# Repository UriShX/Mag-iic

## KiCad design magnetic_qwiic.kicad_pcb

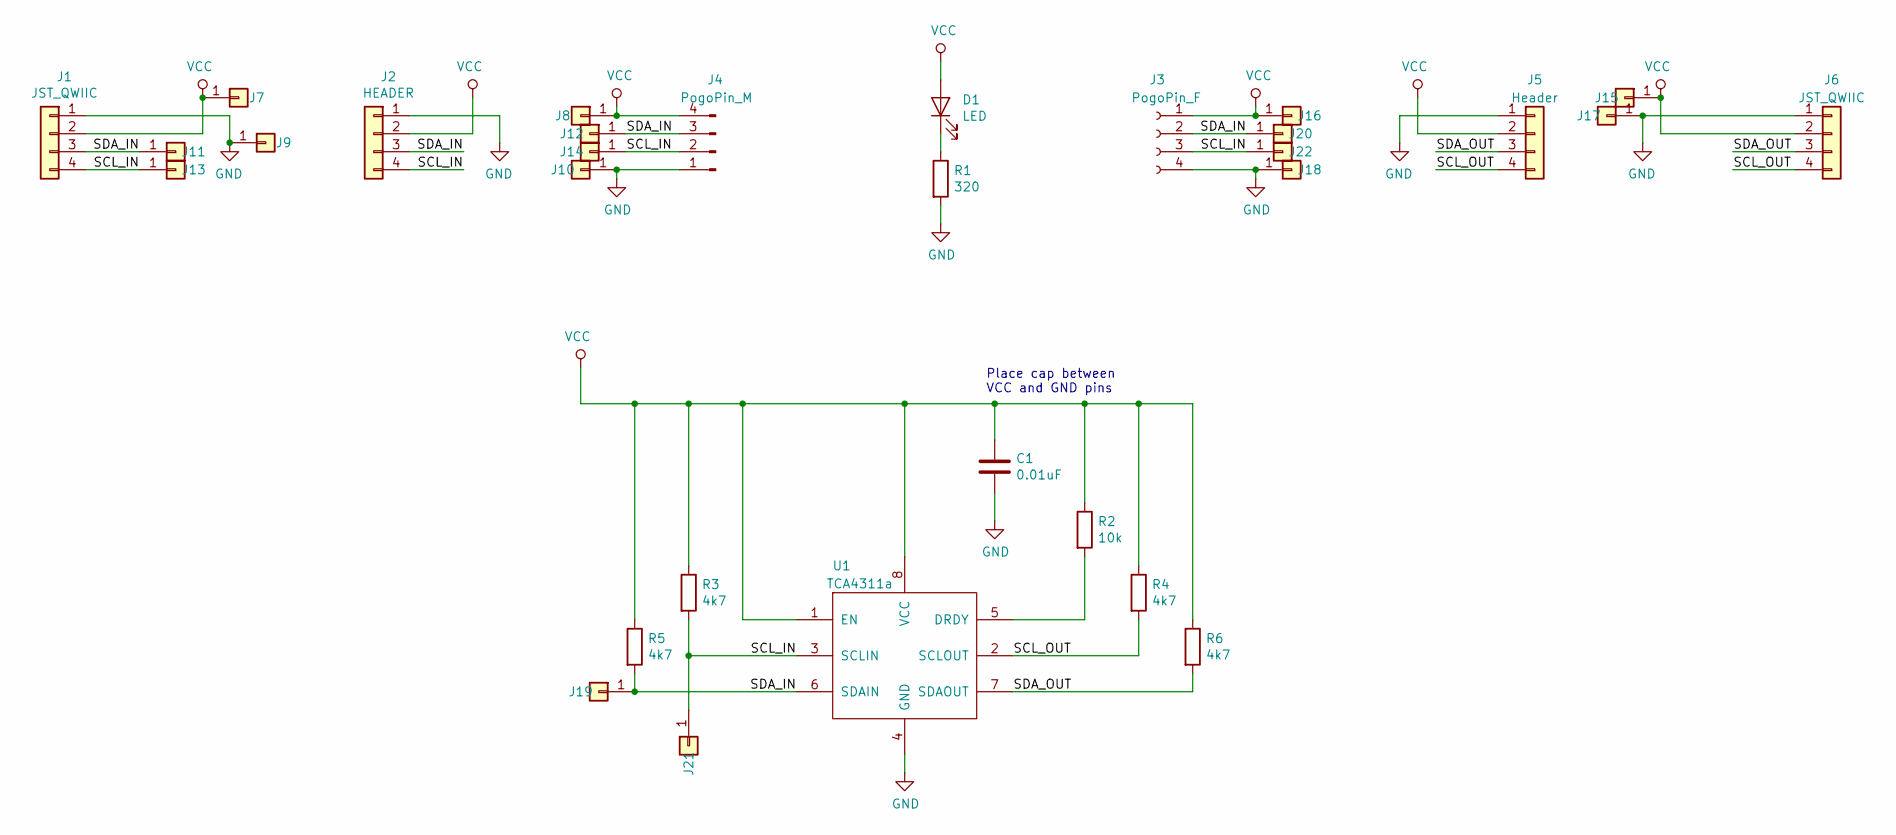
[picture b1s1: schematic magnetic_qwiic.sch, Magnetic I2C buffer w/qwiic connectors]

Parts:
C1: 0.01uF; C_0805_HandSoldering
D1: LED; LED_1206_HandSoldering
J1, J6: JST_QWIIC; JST_SH_SM04B-SRSS-TB_04x1.00mm_Angled
J2: HEADER; Pin_Header_Straight_1x04_Pitch2.54mm
J3: PogoPin_F; QWIIC_PP
J4: PogoPin_M; QWIIC_PP
J5: Header; Pin_Header_Straight_1x04_Pitch2.54mm
J7, J8, J9, J10, J11, J12, J13, J14, J15, J16, J17, J18, J19, J20, J21, J22: Conn_01x01; SMD_pad_for_fillet_solder
R1: 320; R_0805_HandSoldering
R2: 10k; R_0805_HandSoldering
R3, R4, R5, R6: 4k7; R_0805_HandSoldering
U1: TCA4311a; SOIC-8_3.9x4.9mm_Pitch1.27mm

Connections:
/SCL_IN: J1.4, J2.4, J3.3, J4.2, J13.1, J14.1, J21.1, J22.1, R3.2, U1.3 (SCLIN)
/SCL_OUT: J5.4, J6.4, R4.2, U1.2 (SCLOUT)
/SDA_IN: J1.3, J2.3, J3.2, J4.3, J11.1, J12.1, J19.1, J20.1, R5.2, U1.6 (SDAIN)
/SDA_OUT: J5.3, J6.3, R6.2, U1.7 (SDAOUT)
GND: C1.2, J1.1, J2.1, J3.4, J4.1, J5.1, J6.1, J9.1, J10.1, J17.1, J18.1, R1.2, U1.4 (GND)
unnamed: D1.1 (K), R1.1
unnamed: R2.2, U1.5 (DRDY)
VCC: C1.1, D1.2 (A), J1.2, J2.2, J3.1, J4.4, J5.2, J6.2, J7.1, J8.1, J15.1, J16.1, R2.1, R3.1, R4.1, R5.1, R6.1, U1.1 (EN), U1.8 (VCC)

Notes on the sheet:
Place cap between VCC and GND pins

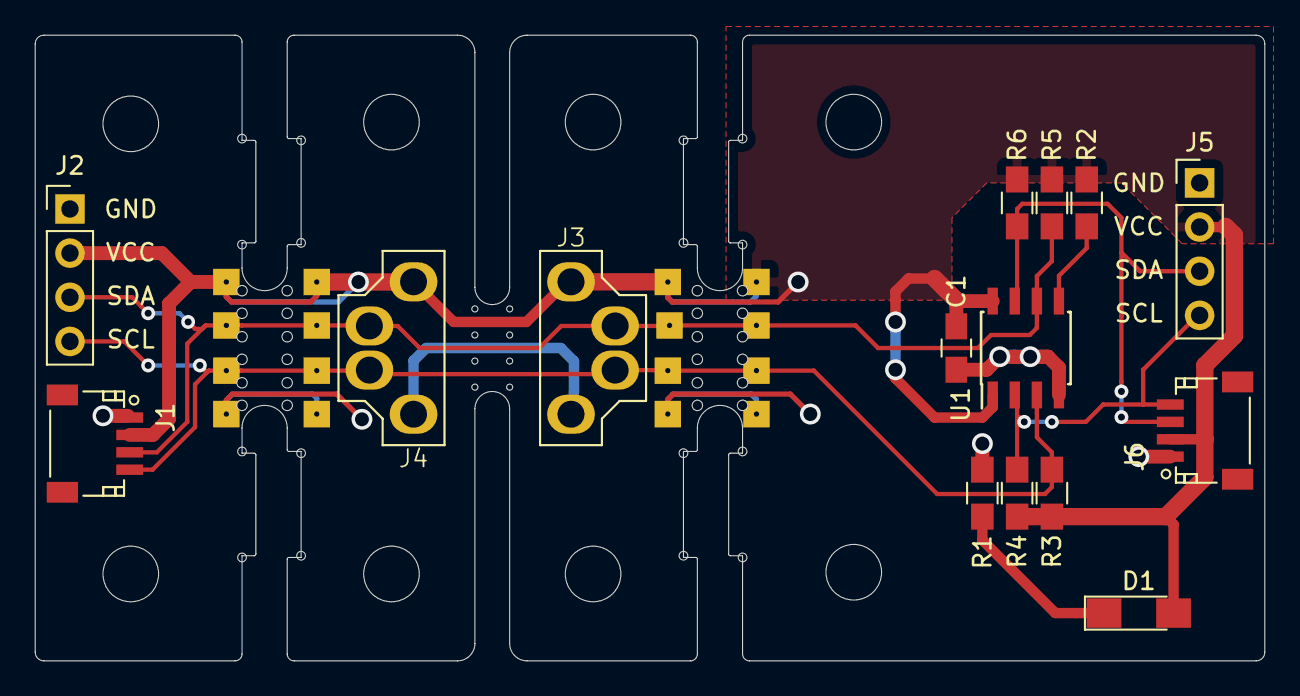
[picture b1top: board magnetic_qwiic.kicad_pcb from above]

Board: 2 copper layers, 70.8 x 36.0 mm, 31 parts (0 on the bottom side), 8 nets.

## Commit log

2020-01-19 first commit
    Date: Sun Jan 19 17:39:42 2020 +0200
    On branch master
    Initial commit
    Changes to be committed:
    new file: README.md
    new file: fp-info-cache
2021-03-29 Rev A mechanical assembly drawing stp and fusion part
2021-03-30 Add history, Rev A based on TCA4311 schematic
